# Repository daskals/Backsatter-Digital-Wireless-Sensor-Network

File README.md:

# Backsatter-Digital-Wireless-Sensor-Network

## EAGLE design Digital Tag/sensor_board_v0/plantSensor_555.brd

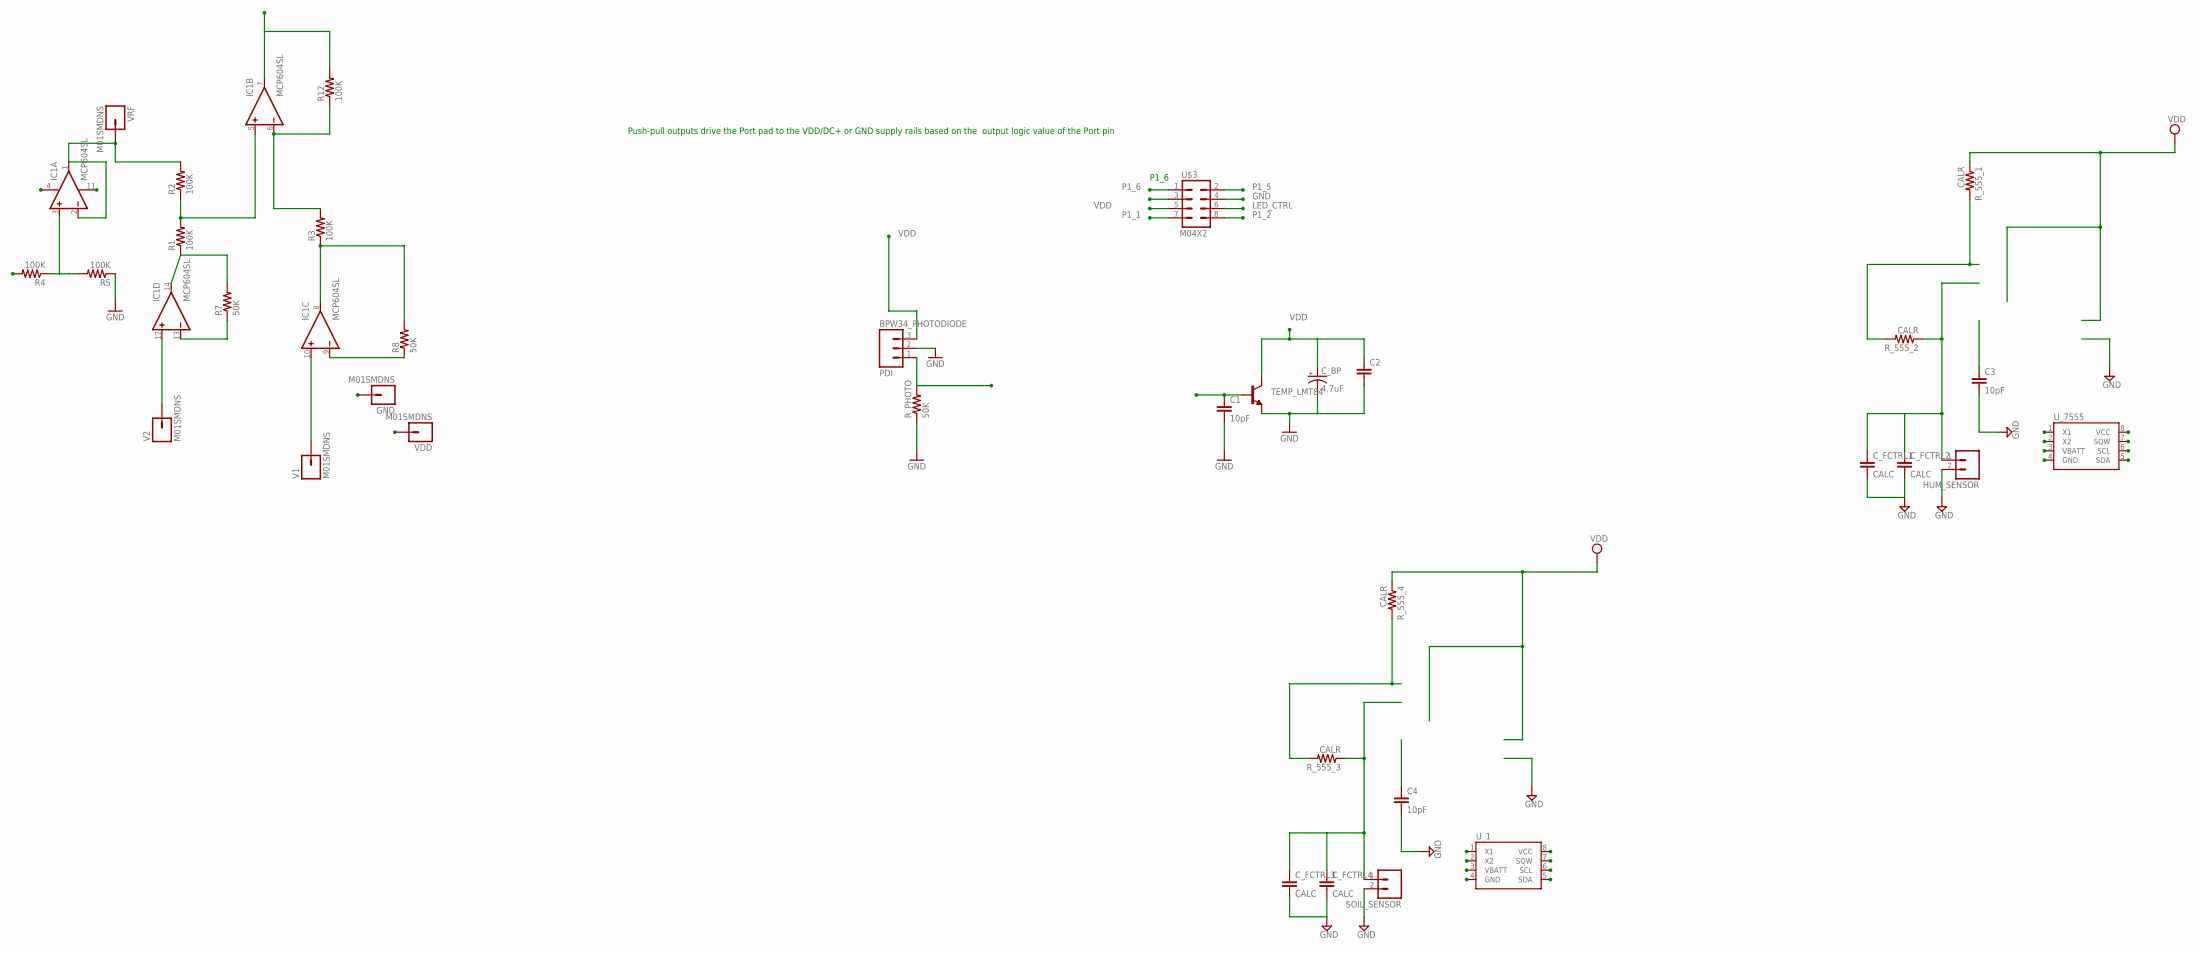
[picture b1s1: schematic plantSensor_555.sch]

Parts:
BPW34_PHOTODIODE: PDI; 1X03
C1, C3, C4: 10pF; 0805
C2: CAP0805; 0805
C_BP: 4.7uF; EIA3216
C_FCTRL1, C_FCTRL2, C_FCTRL3, C_FCTRL4: CALC; 0805
GND: M01SMDNS; 1X01NS
HUM_SENSOR: M02LOCK; 1X02_LOCK
IC1: MCP604SL; SO14
R1, R2, R3, R4, R5, R12: 100K; 0805
R7, R8: 50K; 0805
R_555_1, R_555_2, R_555_3, R_555_4: CALR; 0805
R_PHOTO: 50K; 0805
SOIL_SENSOR: M02LOCK; 1X02_LOCK
TEMP_LMT84: TRANSISTOR_NPNTO92; TO-92
U$3: M04X2; 2X4
U_1, U_7555: DS1307SO8; SO08
V1, V2: M01SMDNS; 1X01NS
VDD: M01SMDNS; 1X01NS
VRF: M01SMDNS; 1X01NS

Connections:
GND: BPW34_PHOTODIODE.2, C1.2, C2.2, C3.2, C4.2, C_BP.C (-), C_FCTRL1.2, C_FCTRL2.2, C_FCTRL3.2, C_FCTRL4.2, GND.1, HUM_SENSOR.2, IC1.11 (V-), R5.1, R_PHOTO.1, SOIL_SENSOR.2, TEMP_LMT84.1 (E), U$3.4, U_1.1 (X1), U_7555.1 (X1)
LED_CTRL: U$3.6
unnamed: IC1.10 (+IN), V1.1
unnamed: IC1.3 (+IN), R4.1, R5.2
unnamed: IC1.13 (-IN), R7.1
unnamed: IC1.12 (+IN), V2.1
unnamed: IC1.5 (+IN), R1.2, R2.1
unnamed: IC1.9 (-IN), R8.1
unnamed: IC1.8 (OUT), R3.1, R8.2
unnamed: IC1.14 (OUT), R1.1, R7.2
unnamed: IC1.6 (-IN), R3.2, R12.1
P1: C4.1, U_1.5 (SDA)
P1_1: IC1.7 (OUT), R12.2, U$3.7
P1_2: C1.1, TEMP_LMT84.2 (B), U$3.8
P1_4: BPW34_PHOTODIODE.1, R_PHOTO.2, U$3.3
P1_5: U$3.2, U_1.3 (VBATT)
P1_6: U$3.1, U_7555.3 (VBATT)
P2: C_FCTRL1.1, C_FCTRL2.1, HUM_SENSOR.1, R_555_2.1, U_7555.2 (X2), U_7555.6 (SCL)
P3: C_FCTRL3.1, C_FCTRL4.1, R_555_3.1, SOIL_SENSOR.1, U_1.2 (X2), U_1.6 (SCL)
P4: R_555_3.2, R_555_4.2, U_1.7 (SQW)
P5: C3.1, U_7555.5 (SDA)
P7: R_555_1.2, R_555_2.2, U_7555.7 (SQW)
VDD: BPW34_PHOTODIODE.3, C2.1, C_BP.A (+), IC1.4 (V+), R4.2, R_555_1.1, R_555_4.1, TEMP_LMT84.3 (C), U$3.5, U_1.4 (GND), U_1.8 (VCC), U_7555.4 (GND), U_7555.8 (VCC), VDD.1
VRF: IC1.1 (OUT), IC1.2 (-IN), R2.2, VRF.1

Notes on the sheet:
Push-pull outputs drive the Port pad to the VDD/DC+ or GND supply rails based on the output logic value of the Port pin
P1_6

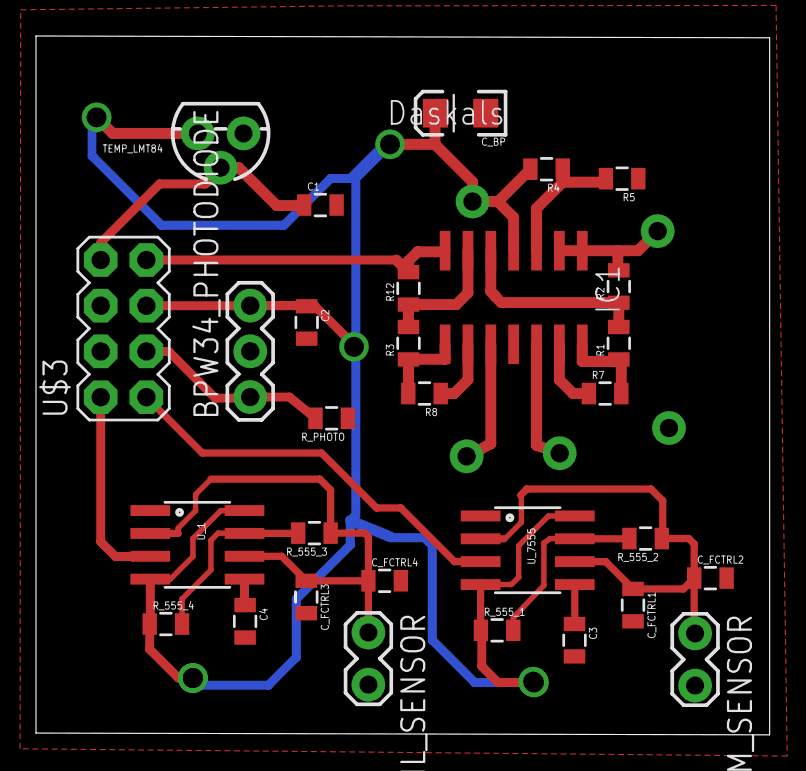
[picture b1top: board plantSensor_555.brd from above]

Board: 2 copper layers, 40.8 x 38.8 mm, 35 parts (0 on the bottom side), 23 nets.

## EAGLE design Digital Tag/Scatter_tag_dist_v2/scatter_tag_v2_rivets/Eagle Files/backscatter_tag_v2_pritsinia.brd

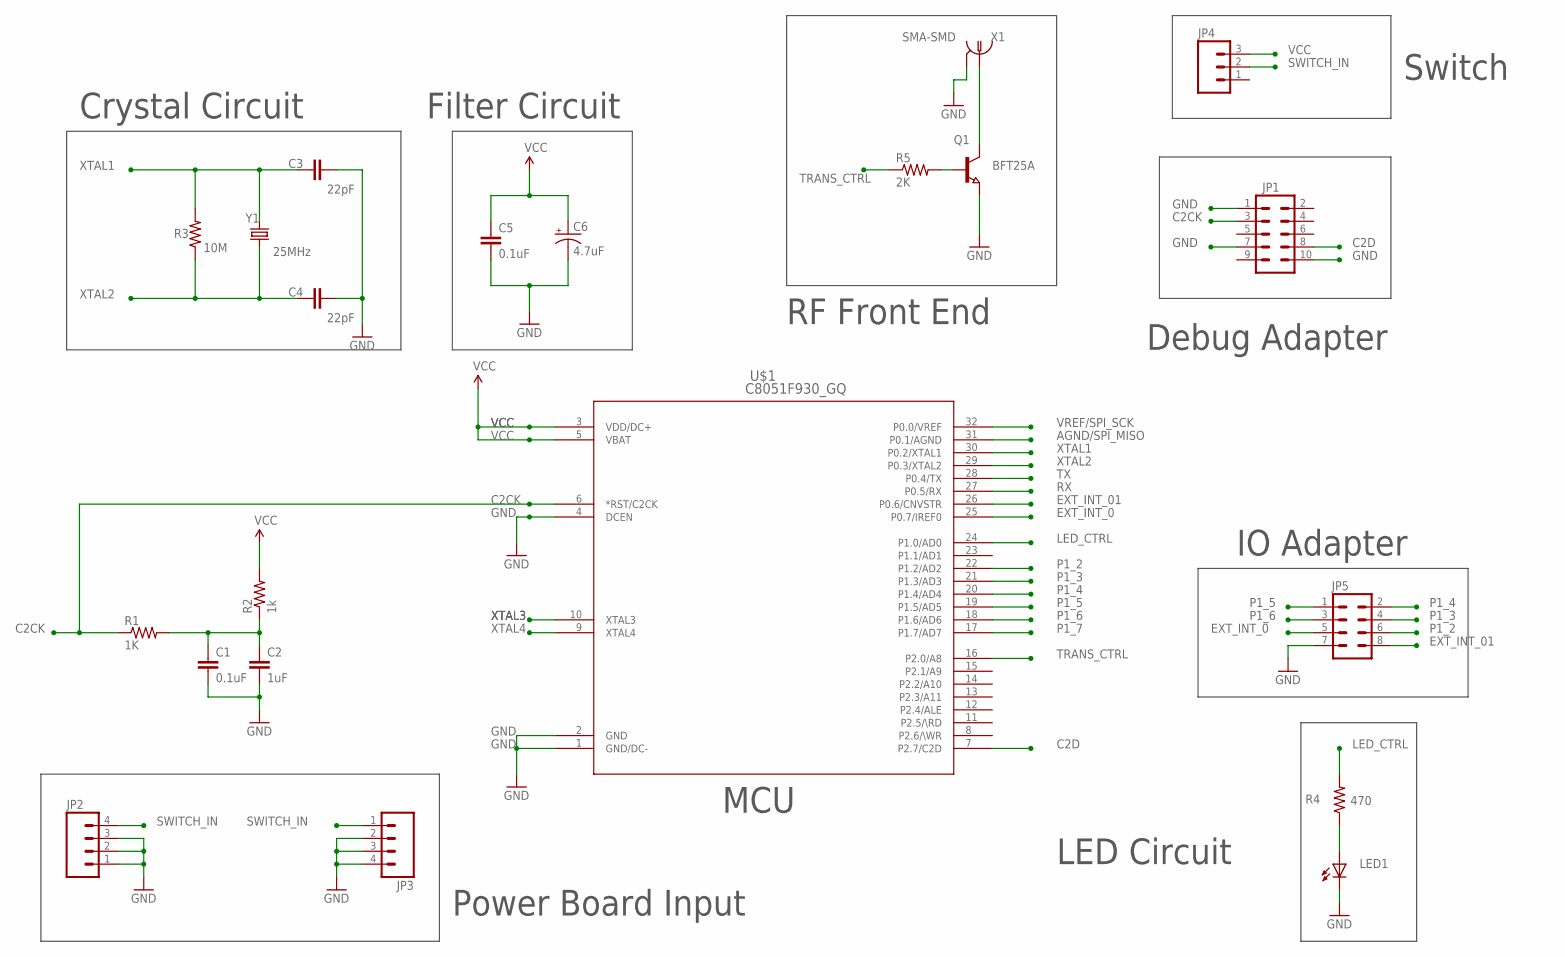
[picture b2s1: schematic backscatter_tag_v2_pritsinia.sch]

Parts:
C1, C5: 0.1uF; 0805
C2: 1uF; 0805
C3, C4: 22pF; 0805
C6: 4.7uF; EIA3216
JP1: M05X2SHD; 2X5-SHROUDED
JP2, JP3: M04LOCK; 1X04_LOCK
JP4: M03LOCK; 1X03_LOCK
JP5: M04X2; 2X4
LED1: LED-FKIT-1206; FKIT-LED-1206
Q1: BFT25A; SOT23
R1: 1K; 0805
R2: 1k; 0805
R3: 10M; 0805
R4: 470; 0805
R5: 2K; 0603-RES
U$1: C8051F930_GQ; QFP32-7X7-0P8MM
X1: SMA-SMD
Y1: 25MHz; HC49US

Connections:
AGND/SPI_MISO: U$1.31 (P0.1/AGND)
C2CK: JP1.3, R1.1, U$1.6 (*RST/C2CK)
C2D: JP1.8, U$1.7 (P2.7/C2D)
EXT_INT_0: JP5.5, U$1.25 (P0.7/IREF0)
EXT_INT_01: JP5.8, U$1.26 (P0.6/CNVSTR)
GND: C1.2, C2.2, C3.2, C4.2, C5.2, C6.C (-), JP1.1, JP1.7, JP1.10, JP2.1, JP2.2, JP2.3, JP3.2, JP3.3, JP3.4, JP5.7, LED1.C, Q1.2 (E), U$1.1 (GND/DC-), U$1.2 (GND), U$1.4 (DCEN), X1.2@1 (2), X1.2@2 (2), X1.2@3 (2), X1.2@4 (2), X1.2@5 (2), X1.2@6 (2)
LED_CTRL: R4.2, U$1.24 (P1.0/AD0)
unnamed: C1.1, C2.1, R1.2, R2.1
unnamed: LED1.A, R4.1
unnamed: Q1.1 (B), R5.2
unnamed: Q1.3 (C), X1.1
P1_2: JP5.6, U$1.22 (P1.2/AD2)
P1_3: JP5.4, U$1.21 (P1.3/AD3)
P1_4: JP5.2, U$1.20 (P1.4/AD4)
P1_5: JP5.1, U$1.19 (P1.5/AD5)
P1_6: JP5.3, U$1.18 (P1.6/AD6)
P1_7: U$1.17 (P1.7/AD7)
RX: U$1.27 (P0.5/RX)
SWITCH_IN: JP2.4, JP3.1, JP4.2
TRANS_CTRL: R5.1, U$1.16 (P2.0/A8)
TX: U$1.28 (P0.4/TX)
VCC: C5.1, C6.A (+), JP4.3, R2.2, U$1.3 (VDD/DC+), U$1.5 (VBAT)
VREF/SPI_SCK: U$1.32 (P0.0/VREF)
XTAL1: C3.1, R3.2, U$1.30 (P0.2/XTAL1), Y1.2
XTAL2: C4.1, R3.1, U$1.29 (P0.3/XTAL2), Y1.1
XTAL3: U$1.10 (XTAL3)
XTAL4: U$1.9 (XTAL4)

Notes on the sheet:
Crystal Circuit
Filter Circuit
RF Front End
Switch
Debug Adapter
IO Adapter
LED Circuit
MCU
Power Board Input

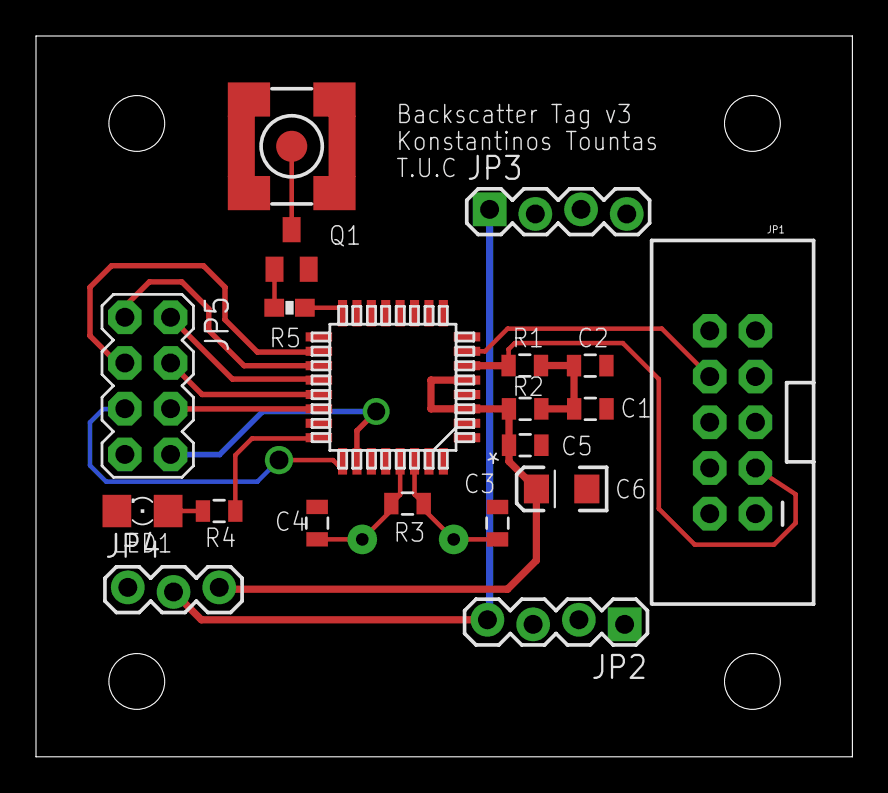
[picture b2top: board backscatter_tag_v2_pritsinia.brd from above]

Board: 2 copper layers, 45.4 x 40.0 mm, 21 parts (1 on the bottom side), 20 nets.

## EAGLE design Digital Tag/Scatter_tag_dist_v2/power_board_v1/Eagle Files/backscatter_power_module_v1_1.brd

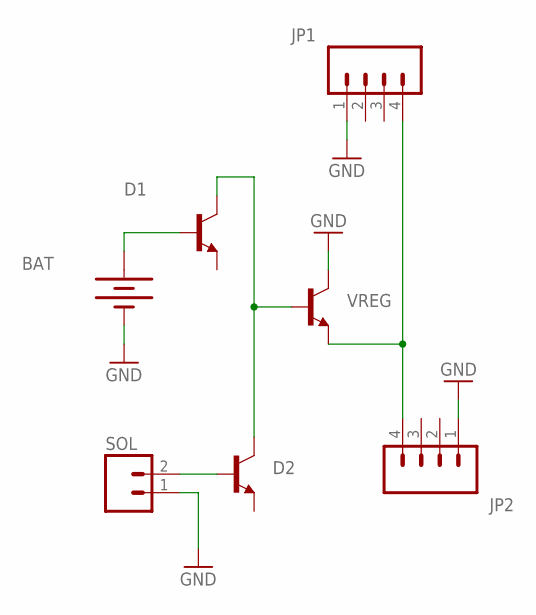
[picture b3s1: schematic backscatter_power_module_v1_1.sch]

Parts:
BAT: BATTERY20PTH_LAB; BATTCOM_20MM_PTH
D1, D2: TRANSISTOR_NPNSOT23; SOT23
JP1, JP2: M04LOCK; 1X04_LOCK
SOL: M02LOCK; 1X02_LOCK
VREG: TRANSISTOR_NPNSOT23; SOT23

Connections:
GND: BAT.2 (-), JP1.1, JP2.1, SOL.1, VREG.3 (C)
unnamed: JP1.4, JP2.4, VREG.2 (E)
unnamed: BAT.1 (+), D1.1 (B)
unnamed: D2.1 (B), SOL.2
unnamed: D1.3 (C), D2.3 (C), VREG.1 (B)

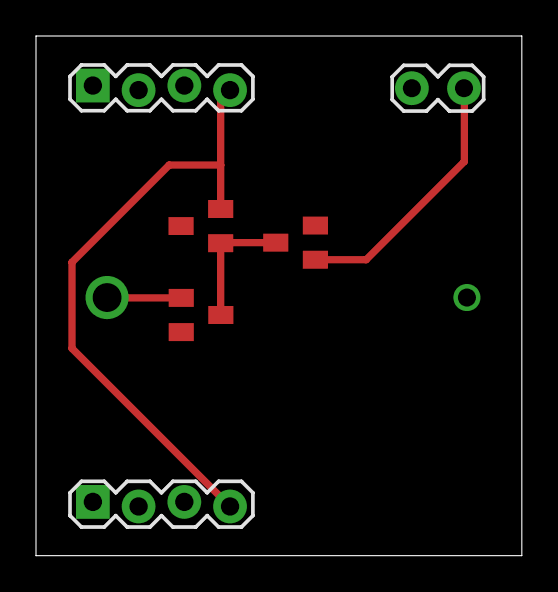
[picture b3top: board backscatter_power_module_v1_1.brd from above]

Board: 2 copper layers, 27.0 x 28.9 mm, 7 parts (1 on the bottom side), 5 nets.

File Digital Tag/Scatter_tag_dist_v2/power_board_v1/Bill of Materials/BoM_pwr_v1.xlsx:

Power Board V1.0
Quantity | Schematic ID | Man. Number | Description | Packaging | Value
2 | JP1, JP2 | 960114-6202-AR | Connector Receptacle 14 Position 0.100" Gold | Through Hole | -
1 | VREG | REF3318AIDBZT | IC VREF SERIES 1.8V SOT23-3 | SOT-23 | -
2 | D1, D2 | BAT54-7-F | Diode Schottky 30V 200mA | SOT-23 | -
1 | BAT | BS-7 | HOLDER COINCELL 2032 RETAINRCLIP | BATTCOM_20MM_PTH | -
1 | SOL | 961114-6404-AR | CONN HEADER VERT SGL 14POS GOLD | Through Hole | -

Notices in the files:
parts and their libraries:
semipassiveTag_library: Licensing: CC v3.0 Share-Alike You are welcome to use this library for commercial purposes.
SparkFun-Capacitors: Licensing: Creative Commons ShareAlike 4.0 International - https://creativecommons.org/licenses/by-sa/4.0
